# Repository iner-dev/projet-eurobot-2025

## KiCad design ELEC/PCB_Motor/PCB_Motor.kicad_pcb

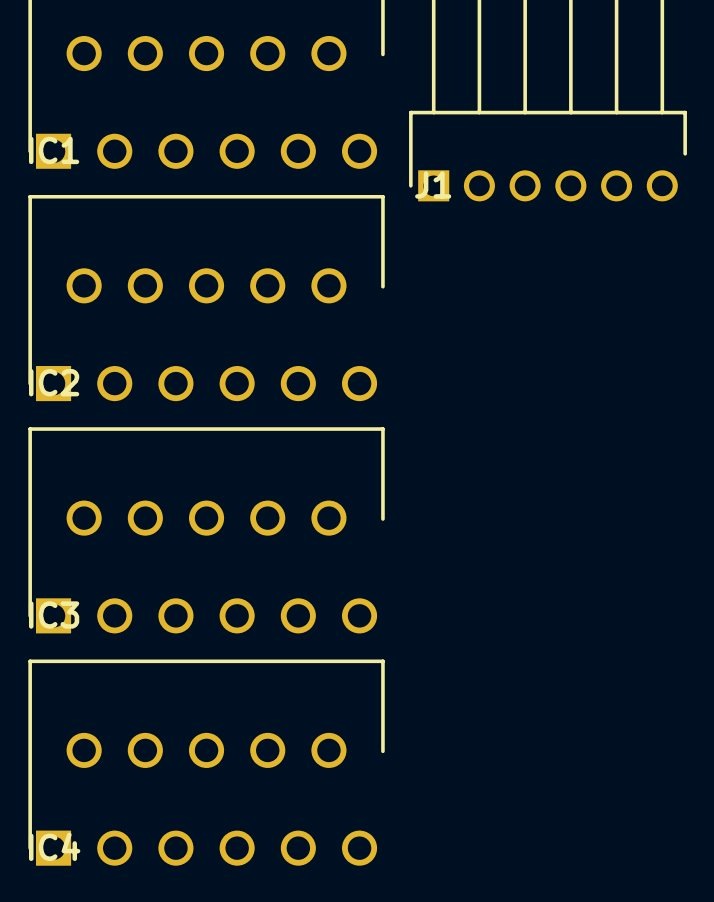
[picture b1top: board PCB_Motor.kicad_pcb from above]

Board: 2 copper layers, 5 parts (0 on the bottom side), 3 nets, no tracks yet.

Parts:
IC1, IC2, IC3, IC4: L6203; TO170P500X1960X2210-11P
J1: Motor A; HDRRA6W66P0X254_1X6_1524X229X249P

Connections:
GND_BAT: IC1.6 (GND), IC2.6 (GND), IC3.6 (GND), IC4.6 (GND)
OUT1_A: IC1.3 (OUT1), J1.1, J1.2, J1.3, J1.4, J1.5, J1.6
VCC_BAT: IC1.2 (VS), IC2.2 (VS), IC3.2 (VS), IC4.2 (VS)

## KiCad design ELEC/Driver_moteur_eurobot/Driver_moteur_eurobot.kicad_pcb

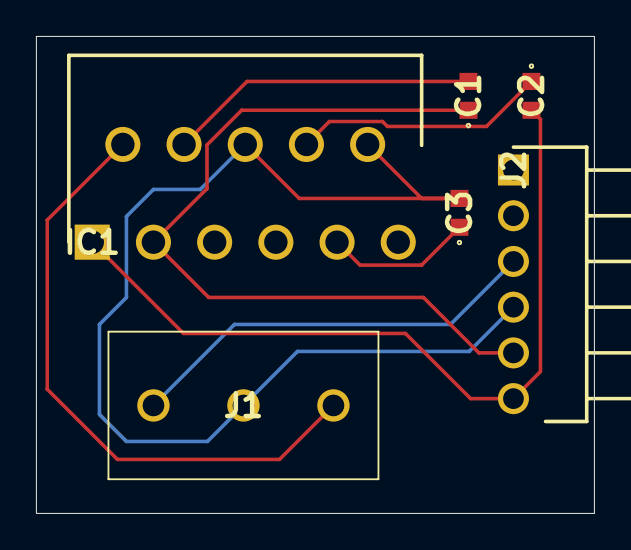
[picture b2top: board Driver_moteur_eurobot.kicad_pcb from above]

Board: 2 copper layers, 31.0 x 26.5 mm, 6 parts (0 on the bottom side), 8 nets.

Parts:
C1, C2, C3: C0603X153K5RACTU; C0603
IC1: L6203; TO170P500X1960X2210-11P
J1: 282836-3; 2828363
J2: 22-28-8063; HDRRA6W66P0X254_1X6_1524X229X249P

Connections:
+5V: J1.1, J2.3
GND: C3.2, IC1.6 (GND), IC1.10 (SENSE), J1.2, J2.4
unnamed: C1.2, IC1.4 (BOOT1)
unnamed: C2.1, IC1.8 (BOOT2)
unnamed: C3.1, IC1.9 (VREF)
OUT1: C1.1, IC1.3 (OUT1), J2.5
OUT2: C2.2, IC1.1 (OUT2), J2.6
VCC: IC1.2 (VS), J1.3

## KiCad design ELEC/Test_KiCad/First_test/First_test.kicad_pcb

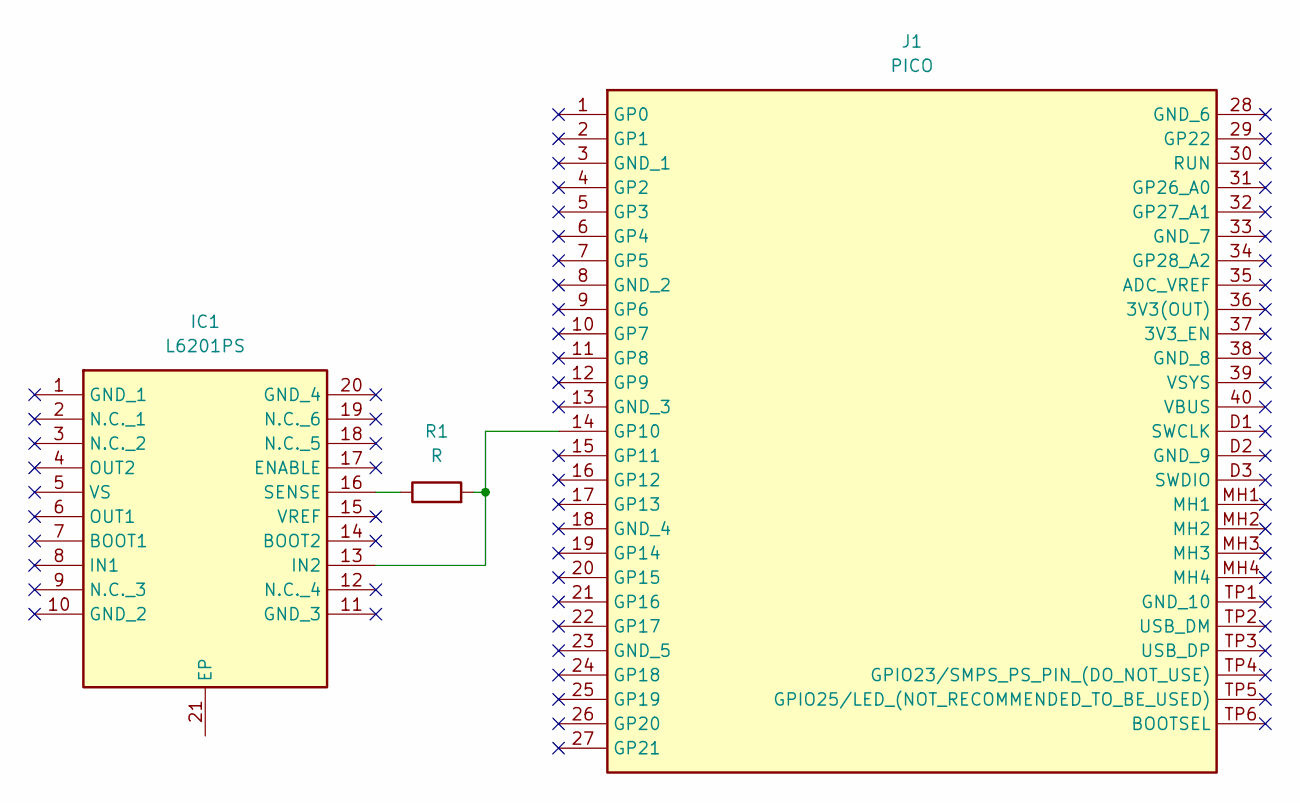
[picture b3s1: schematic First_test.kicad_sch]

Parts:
IC1: L6201PS; SOIC127P1420X360-21N; Manufacturer_Part_Number L6201PS; Mouser Part Number 511-L6201PS
J1: PICO; Manufacturer_Part_Number PICO
R1: R; R_Box_L8.4mm_W2.5mm_P5.08mm

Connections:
unnamed: IC1.13 (IN2), J1.14 (GP10), R1.2
unnamed: IC1.16 (SENSE), R1.1

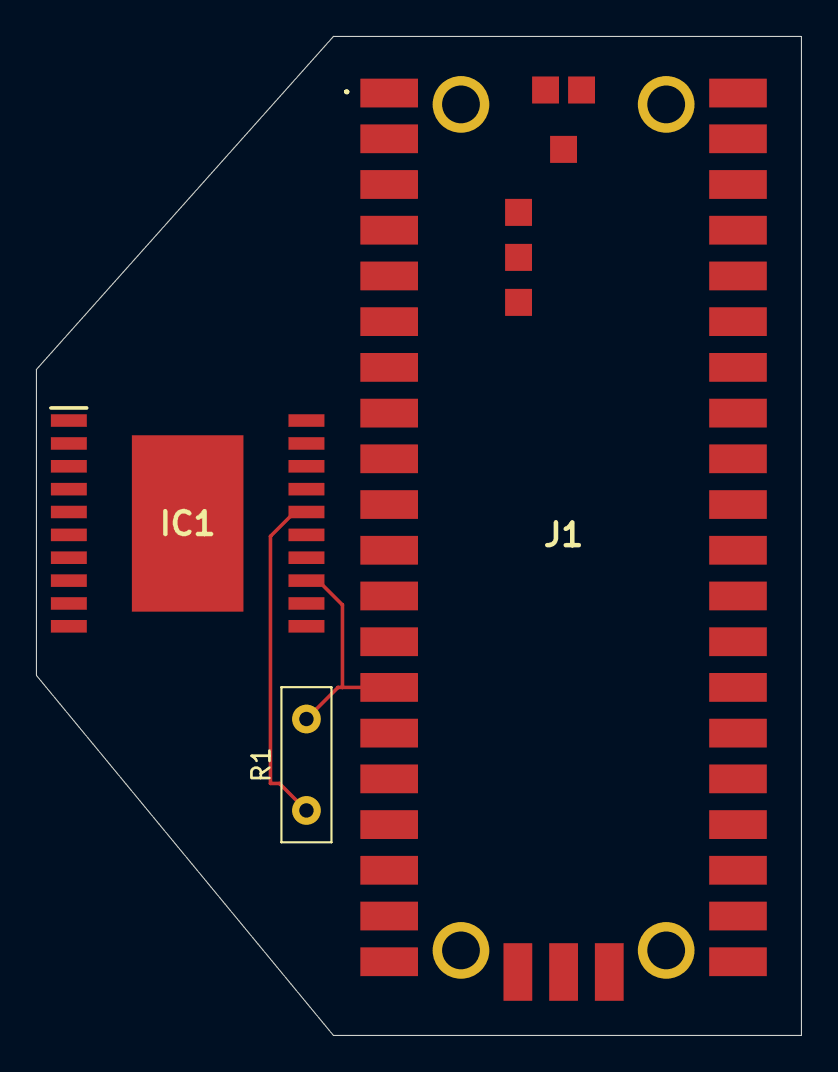
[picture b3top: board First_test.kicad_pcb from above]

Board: 2 copper layers, 42.5 x 55.5 mm, 3 parts (0 on the bottom side), 2 nets.

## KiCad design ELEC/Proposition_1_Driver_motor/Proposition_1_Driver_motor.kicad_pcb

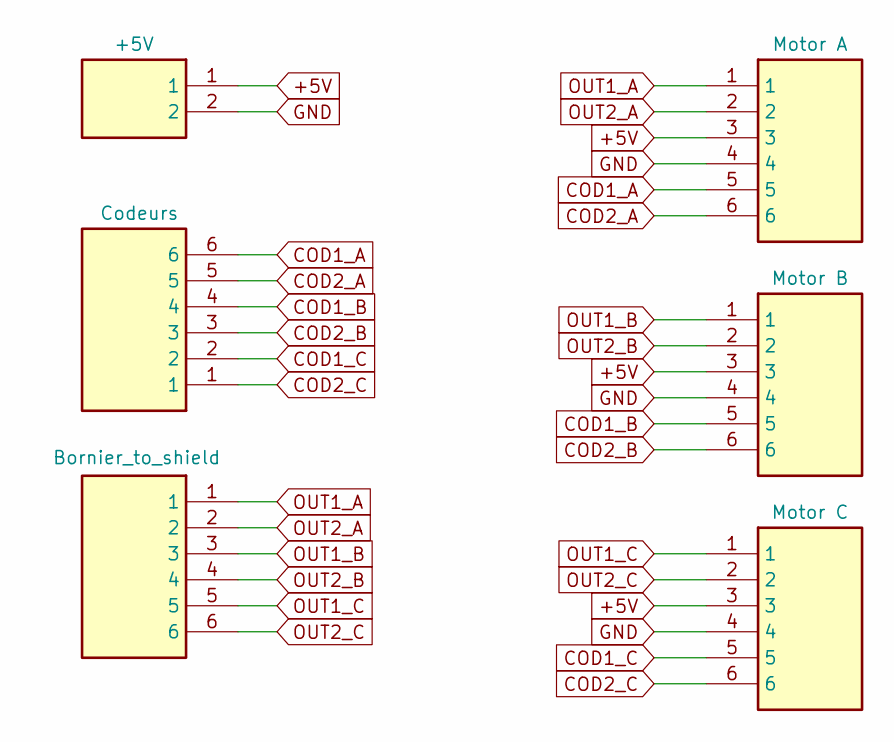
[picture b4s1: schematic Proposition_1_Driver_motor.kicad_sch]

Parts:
J1, J3, J5, J6: 22-28-8063; HDRRA6W66P0X254_1X6_1524X229X249P; Manufacturer_Part_Number 22-28-8063
J2: 796638-6; SHDR6W102P0X508_1X6_3230X1200X850P; Manufacturer_Part_Number 796638-6
J4: TMM-102-03-G-S; HDRV2W50P0X200_1X2_400X197X550P; Manufacturer_Part_Number TMM-102-03-G-S

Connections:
+5V: J1.3, J4.1, J5.3, J6.3
COD1_A: J1.5, J3.6
COD1_B: J3.4, J5.5
COD1_C: J3.2, J6.5
COD2_A: J1.6, J3.5
COD2_B: J3.3, J5.6
COD2_C: J3.1, J6.6
GND: J1.4, J4.2, J5.4, J6.4
OUT1_A: J1.1, J2.1
OUT1_B: J2.3, J5.1
OUT1_C: J2.5, J6.1
OUT2_A: J1.2, J2.2
OUT2_B: J2.4, J5.2
OUT2_C: J2.6, J6.2

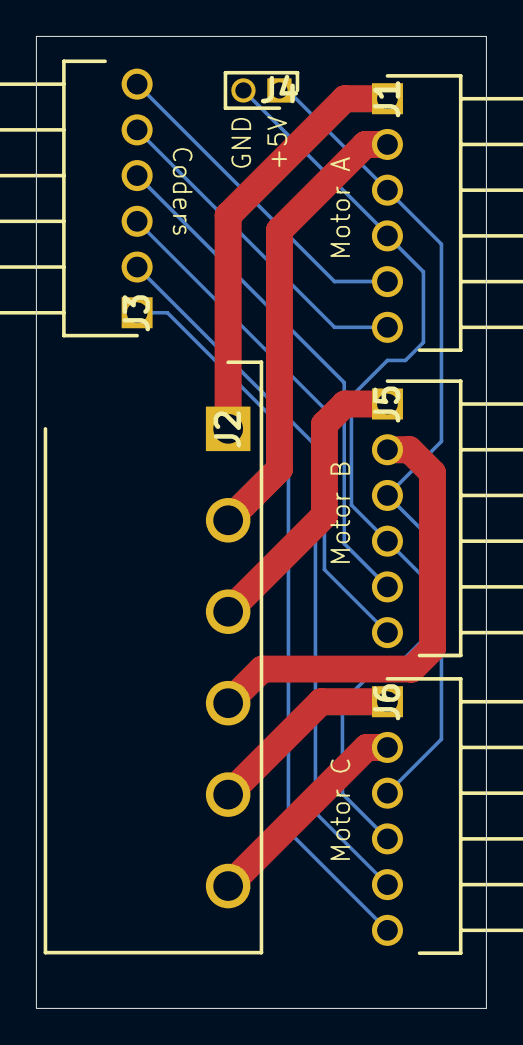
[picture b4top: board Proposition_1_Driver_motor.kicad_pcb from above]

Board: 2 copper layers, 25.0 x 54.0 mm, 6 parts (0 on the bottom side), 14 nets.

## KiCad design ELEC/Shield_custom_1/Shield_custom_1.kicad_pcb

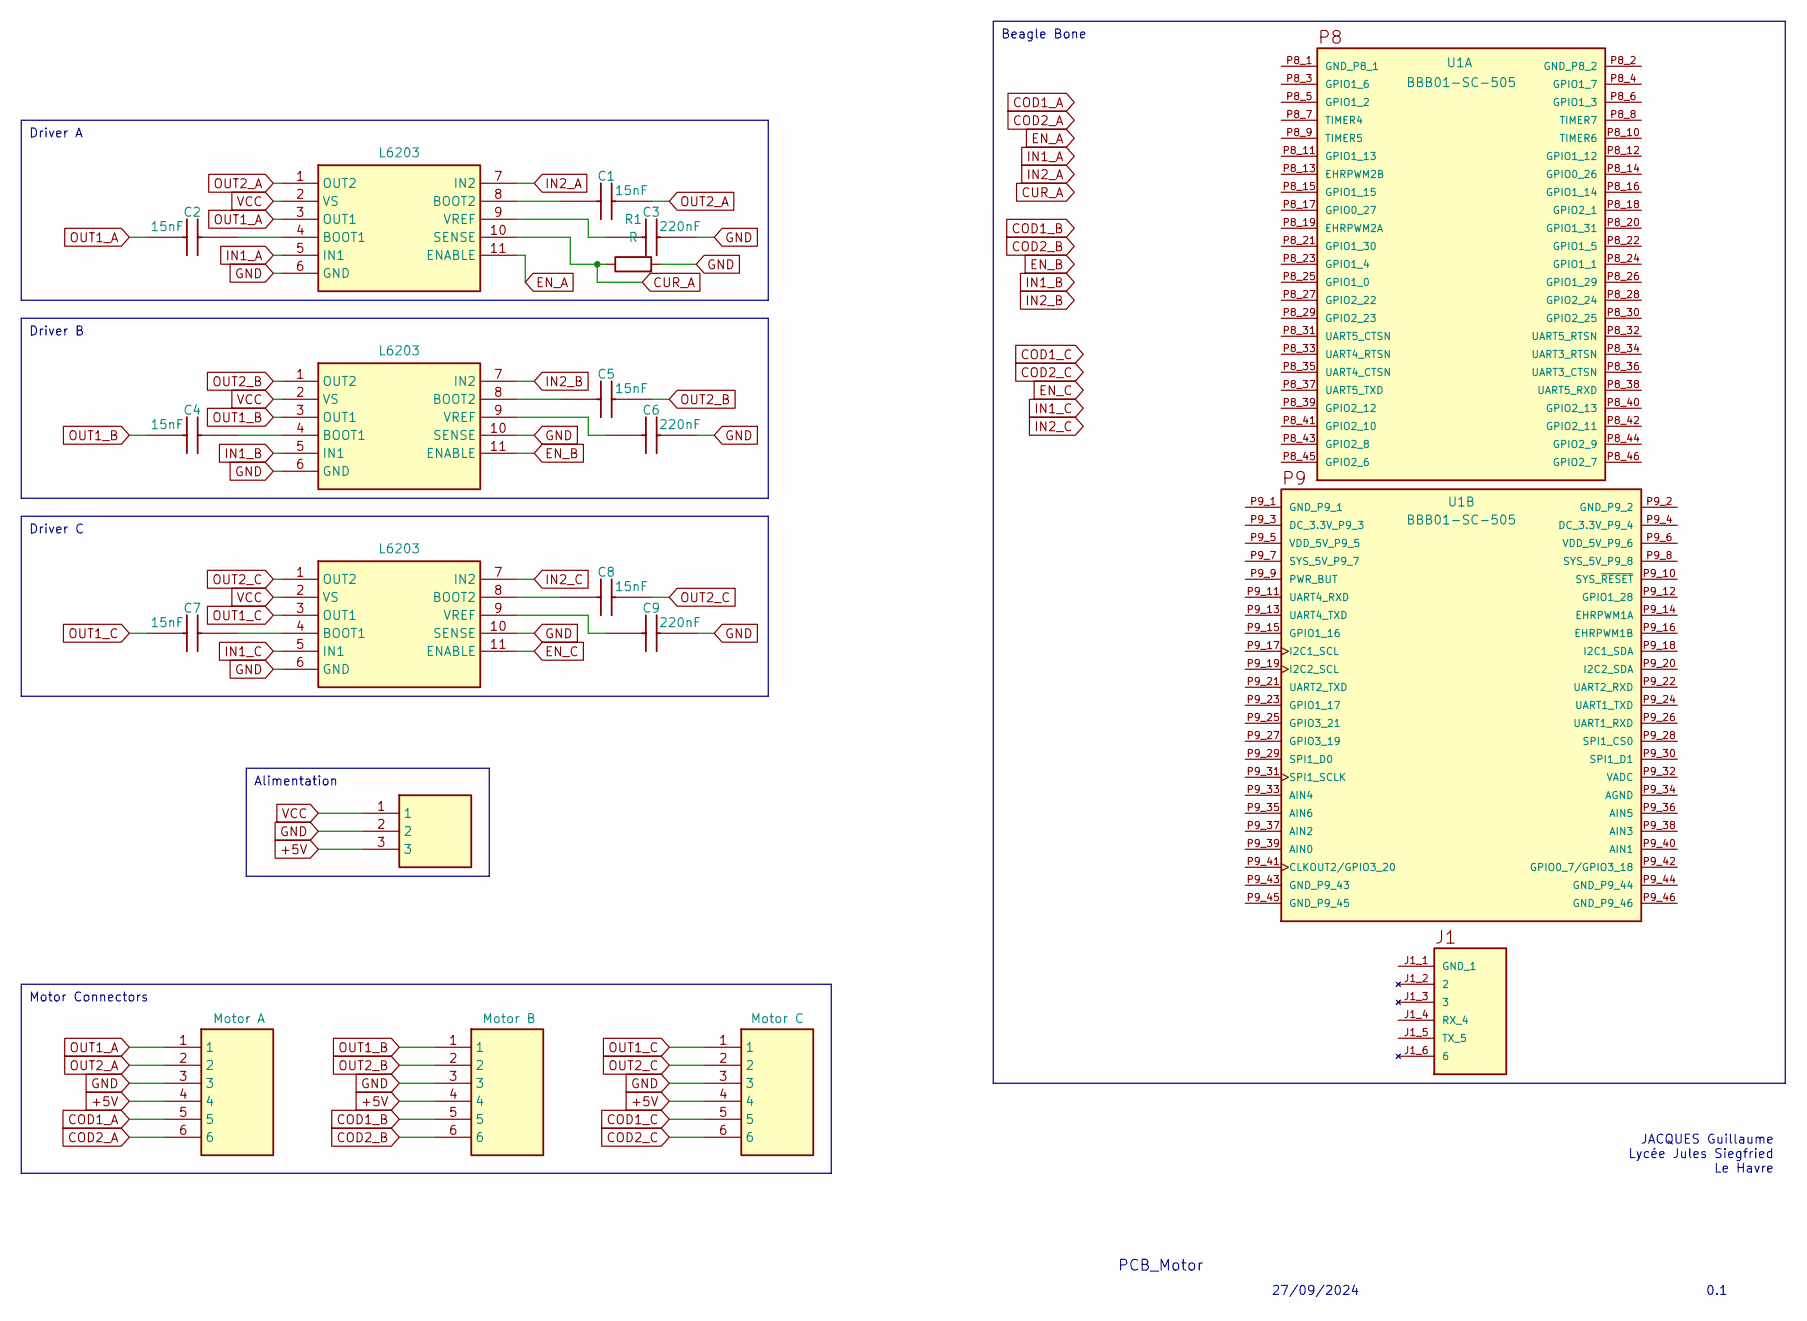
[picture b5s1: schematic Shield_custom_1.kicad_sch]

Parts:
C1, C2, C4, C5, C7, C8: 15nF; C0603; Manufacturer_Part_Number C0603X153K5RACTU
C3, C6, C9: 220nF; C0603; Manufacturer_Part_Number C0603X153K5RACTU
IC1, IC2, IC3: L6203; TO170P500X1960X2210-11P; Manufacturer_Part_Number L6203
J1, J2, J3: HTSW-106-07-G-S; HDRV6W64P0X254_1X6_1524X254X838P; Mouser Part Number 200-HTSW10607GS
J8: 282836-3; 2828363; Manufacturer_Part_Number 282836-3
R1: R
U1: BBB01-SC-505; MODULE_BBB01-SC-505; PARTREV C

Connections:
+5V: J1.4, J2.4, J3.4, J8.3
COD1_A: J1.5
COD1_B: J2.5
COD1_C: J3.5
COD2_A: J1.6
COD2_B: J2.6
COD2_C: J3.6
EN_A: IC1.11 (ENABLE)
EN_B: IC2.11 (ENABLE)
EN_C: IC3.11 (ENABLE)
IN1_A: IC1.5 (IN1)
IN1_B: IC2.5 (IN1)
IN1_C: IC3.5 (IN1)
IN2_A: IC1.7 (IN2)
IN2_B: IC2.7 (IN2)
IN2_C: IC3.7 (IN2)
unnamed: C2.2, IC1.4 (BOOT1)
unnamed: C1.1, IC1.8 (BOOT2)
unnamed: C3.1, IC1.9 (VREF)
unnamed: C4.2, IC2.4 (BOOT1)
unnamed: C5.1, IC2.8 (BOOT2)
unnamed: C6.1, IC2.9 (VREF)
unnamed: C7.2, IC3.4 (BOOT1)
unnamed: C8.1, IC3.8 (BOOT2)
unnamed: C9.1, IC3.9 (VREF)
OUT1_A: C2.1, IC1.3 (OUT1), J1.1
OUT1_B: C4.1, IC2.3 (OUT1), J2.1
OUT1_C: C7.1, IC3.3 (OUT1), J3.1
OUT2_A: C1.2, IC1.1 (OUT2), J1.2
OUT2_B: C5.2, IC2.1 (OUT2), J2.2
OUT2_C: C8.2, IC3.1 (OUT2), J3.2
VCC: IC1.2 (VS), IC2.2 (VS), IC3.2 (VS), J8.1

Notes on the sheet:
Driver C
Driver A
Alimentation
Motor Connectors
Beagle Bone
Driver B
0.1
PCB_Motor
27/09/2024
JACQUES Guillaume Lycée Jules Siegfried Le Havre

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
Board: 2 copper layers, 17 parts (0 on the bottom side), 18 nets, no tracks yet.

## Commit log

2024-10-06 append archives 2024
2024-10-07 upd: class
2024-10-07 add class 2
2024-10-08 first_save
2024-10-14 set pami
2024-11-25 sasha1
2024-12-06 MAJ
    ea'g
2024-12-06 LALAL
2024-12-06 lalilu
2024-12-06 6/12
2024-12-12 pprt
2024-12-16 16/12/24
2025-01-10 main move
